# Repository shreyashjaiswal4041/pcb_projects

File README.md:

# pcb_projects
🛠 Tools & Software Used
	•	🖥 KiCad

  🧩 Key Features
	•	✅ Proper grounding strategy (Star / Split Ground / Solid GND Plane)
	•	✅ Controlled trace width for current handling
	•	✅ Decoupling capacitor placement best practices
	•	✅ EMI-aware routing
	•	✅ Thermal management considerations
	•	✅ Silkscreen labeling for assembly

  /hardware
   ├── schematic.kicad_sch
   ├── pcb_layout.kicad_pcb
   ├── gerbers/
   ├── BOM.csv
   ├── 3D_model/
   └── fabrication_files/

/docs
   ├── block_diagram.png
   ├── pcb_top_view.png
   ├── pcb_bottom_view.png

   🧪 Design Validation
	•	ERC passed ✔
	•	DRC passed ✔
	•	Clearance rules verified ✔
	•	Power integrity reviewed ✔
	•	Thermal considerations analyzed ✔

  📈 Learning Outcomes

Through this project, I gained experience in:
	•	PCB stack-up planning
	•	Power routing techniques
	•	Decoupling strategies
	•	EMI reduction
	•	Manufacturability optimization
	•	Hardware debugging

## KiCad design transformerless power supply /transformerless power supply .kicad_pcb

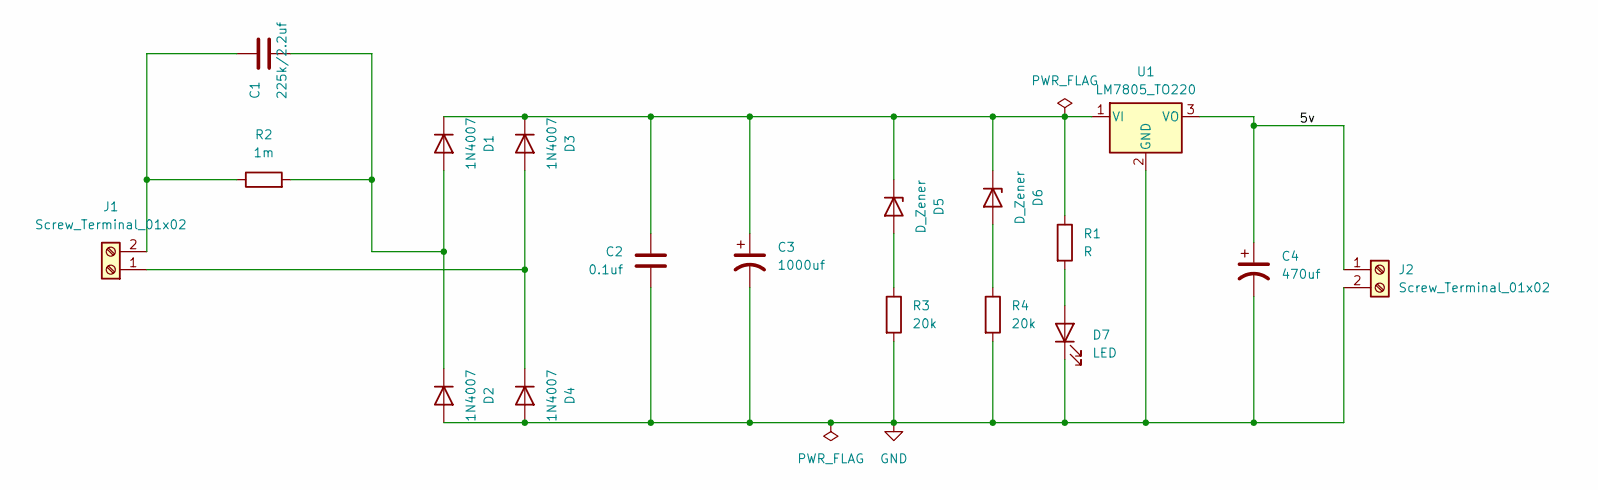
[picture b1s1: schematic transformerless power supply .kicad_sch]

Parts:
C1: 225k/2.2uf; C_Rect_L18.0mm_W6.0mm_P15.00mm_FKS3_FKP3
C2: 0.1uf; C_Disc_D4.7mm_W2.5mm_P5.00mm
C3: 1000uf; C_Radial_D10.0mm_H12.5mm_P5.00mm
C4: 470uf; C_Radial_D10.0mm_H12.5mm_P5.00mm
D1, D2, D3, D4: 1N4007; D_DO-41_SOD81_P10.16mm_Horizontal
D5, D6: D_Zener; D_A-405_P7.62mm_Horizontal
D7: LED; LED_D5.0mm
J1, J2: Screw_Terminal_01x02; TerminalBlock_Xinya_XY308-2.54-2P_1x02_P2.54mm_Horizontal
R1: R; R_Axial_DIN0207_L6.3mm_D2.5mm_P7.62mm_Horizontal
R2: 1m; R_Axial_DIN0207_L6.3mm_D2.5mm_P7.62mm_Horizontal
R3, R4: 20k; R_Axial_DIN0207_L6.3mm_D2.5mm_P7.62mm_Horizontal
U1: LM7805_TO220; TO-220-3_Vertical

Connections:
/5v: C4.1, J2.1, U1.3 (VO)
GND: C2.2, C3.2, C4.2, D2.2 (A), D4.2 (A), D7.1 (K), J2.2, R3.2, R4.2, U1.2 (GND)
unnamed: C1.2, D1.2 (A), D2.1 (K), R2.2
unnamed: C2.1, C3.1, D1.1 (K), D3.1 (K), D5.1 (K), D6.1 (K), R1.1, U1.1 (VI)
unnamed: D3.2 (A), D4.1 (K), J1.1
unnamed: D5.2 (A), R3.1
unnamed: D6.2 (A), R4.1
unnamed: D7.2 (A), R1.2
unnamed: C1.1, J1.2, R2.1

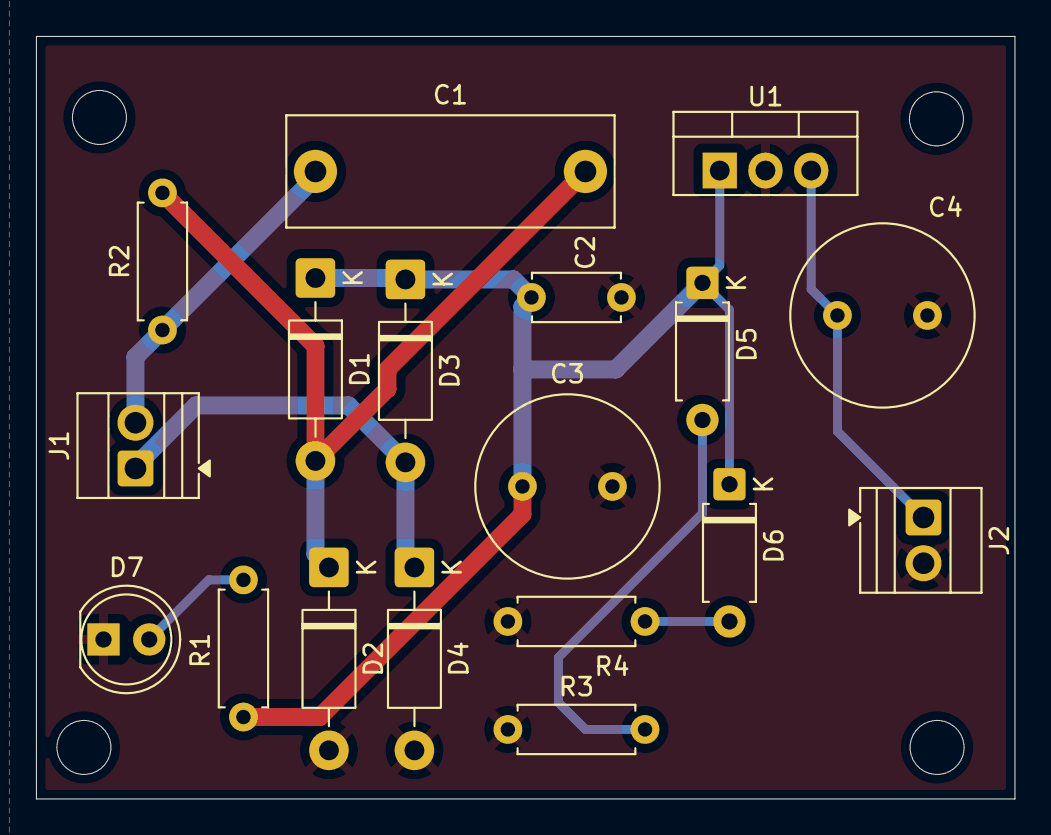
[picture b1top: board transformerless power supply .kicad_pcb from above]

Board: 2 copper layers, 54.4 x 42.4 mm, 18 parts (0 on the bottom side), 9 nets.

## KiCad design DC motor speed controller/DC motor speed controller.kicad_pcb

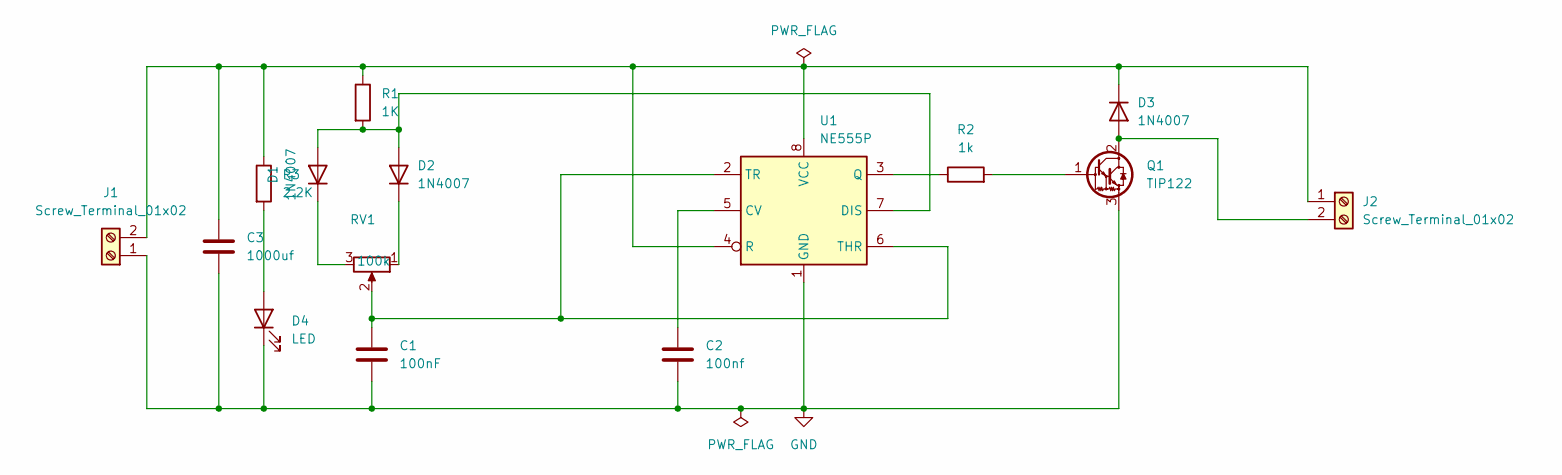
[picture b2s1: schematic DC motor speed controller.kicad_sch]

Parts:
C1: 100nF; C_Disc_D4.7mm_W2.5mm_P5.00mm
C2: 100nf; C_Disc_D4.7mm_W2.5mm_P5.00mm
C3: 1000uf; CP_Radial_D10.0mm_P5.00mm
D1, D2, D3: 1N4007; D_DO-41_SOD81_P10.16mm_Horizontal
D4: LED; LED_D5.0mm
J1, J2: Screw_Terminal_01x02; TerminalBlock_MaiXu_MX126-5.0-02P_1x02_P5.00mm
Q1: TIP122; TO-220-3_Vertical
R1: 1K; R_Axial_DIN0204_L3.6mm_D1.6mm_P7.62mm_Horizontal
R2: 1k; R_Axial_DIN0204_L3.6mm_D1.6mm_P7.62mm_Horizontal
R3: 2.2K; R_Axial_DIN0204_L3.6mm_D1.6mm_P7.62mm_Horizontal
RV1: 100k; Potentiometer_Alps_RK163_Single_Horizontal
U1: NE555P; DIP-8_W7.62mm

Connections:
GND: C1.2, C2.2, C3.2, D4.1 (K), J1.1, Q1.3 (E), U1.1 (GND)
unnamed: D1.2 (A), D2.2 (A), R1.2, U1.7 (DIS)
unnamed: D1.1 (K), RV1.3
unnamed: D2.1 (K), RV1.1
unnamed: D3.2 (A), J2.2, Q1.2 (C)
unnamed: C3.1, D3.1 (K), J1.2, J2.1, R1.1, R3.1, U1.4 (R), U1.8 (VCC)
unnamed: D4.2 (A), R3.2
unnamed: Q1.1 (B), R2.2
unnamed: C2.1, U1.5 (CV)
unnamed: R2.1, U1.3 (Q)
unnamed: C1.1, RV1.2, U1.2 (TR), U1.6 (THR)

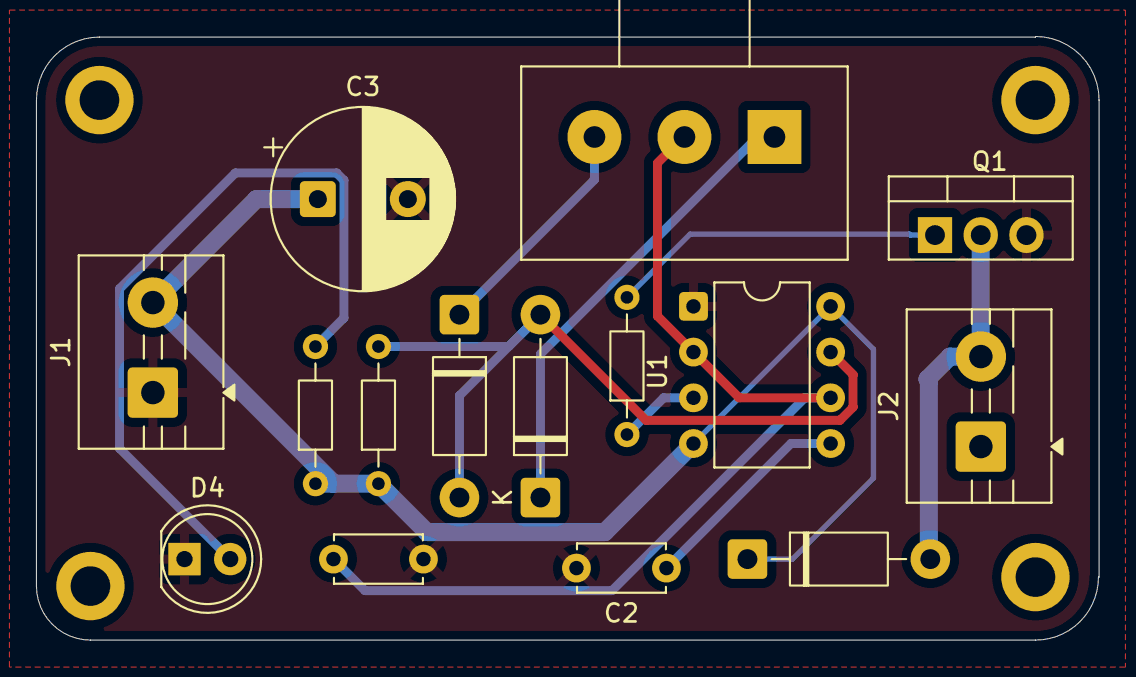
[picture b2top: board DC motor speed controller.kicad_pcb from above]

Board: 2 copper layers, 59.0 x 33.5 mm, 15 parts (0 on the bottom side), 11 nets.

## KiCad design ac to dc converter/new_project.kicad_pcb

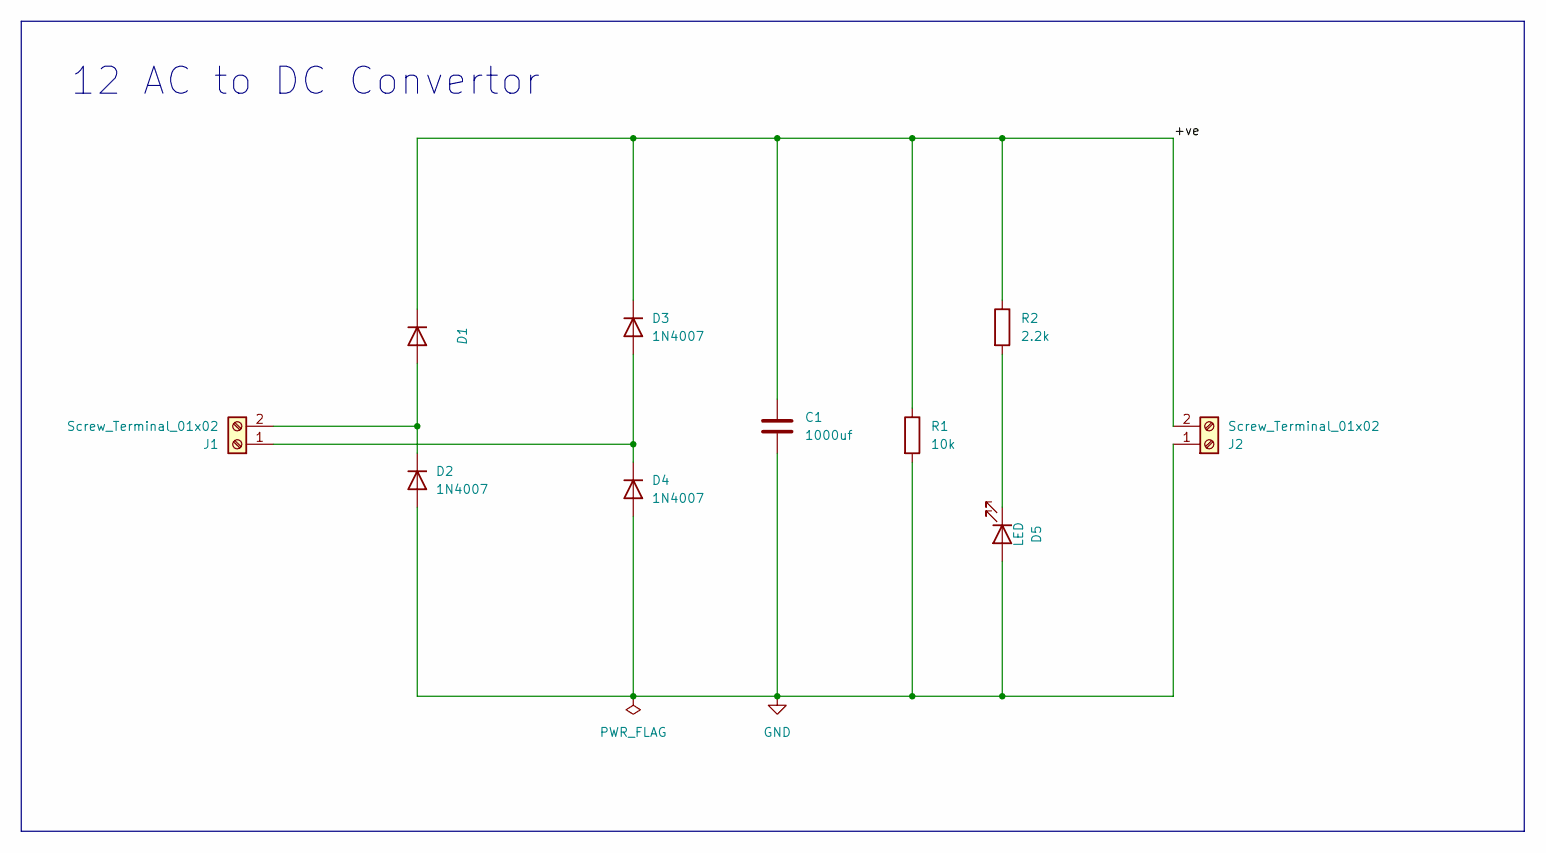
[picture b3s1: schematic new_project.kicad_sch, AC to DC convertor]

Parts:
C1: 1000uf; C_Radial_D8.0mm_H11.5mm_P3.50mm
D1, D2, D3, D4: 1N4007; D_DO-41_SOD81_P10.16mm_Horizontal
D5: LED; LED_D4.0mm
J1, J2: Screw_Terminal_01x02; TerminalBlock_Xinya_XY308-2.54-2P_1x02_P2.54mm_Horizontal
R1: 10k; R_Axial_DIN0207_L6.3mm_D2.5mm_P7.62mm_Horizontal
R2: 2.2k; R_Axial_DIN0207_L6.3mm_D2.5mm_P7.62mm_Horizontal

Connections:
/+ve: C1.1, D1.1 (K), D3.1 (K), J2.2, R1.1, R2.1
GND: C1.2, D2.2 (A), D4.2 (A), D5.2 (A), J2.1, R1.2
unnamed: D1.2 (A), D2.1 (K), J1.2
unnamed: D3.2 (A), D4.1 (K), J1.1
unnamed: D5.1 (K), R2.2

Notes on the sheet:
12 AC to DC Convertor

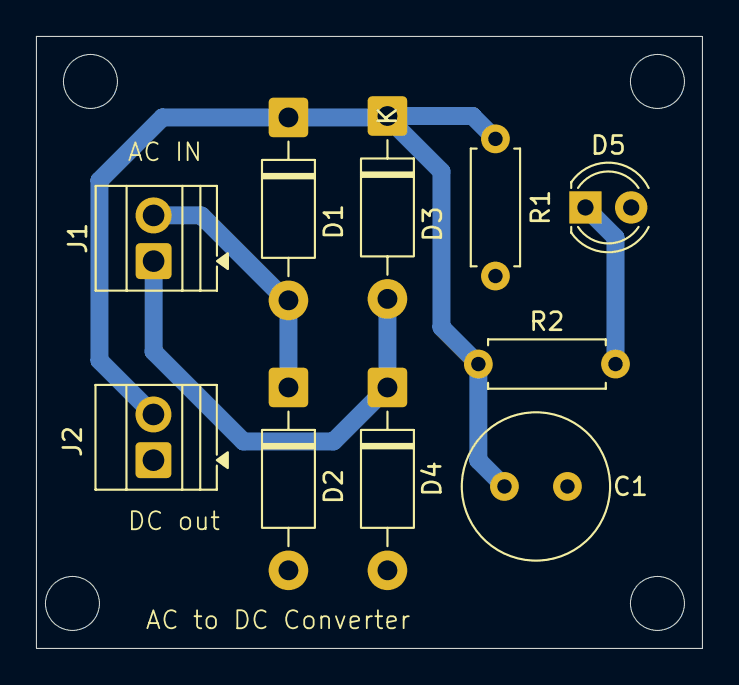
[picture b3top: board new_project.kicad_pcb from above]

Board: 2 copper layers, 37.0 x 34.0 mm, 10 parts (0 on the bottom side), 5 nets.

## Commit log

2026-02-20 README
